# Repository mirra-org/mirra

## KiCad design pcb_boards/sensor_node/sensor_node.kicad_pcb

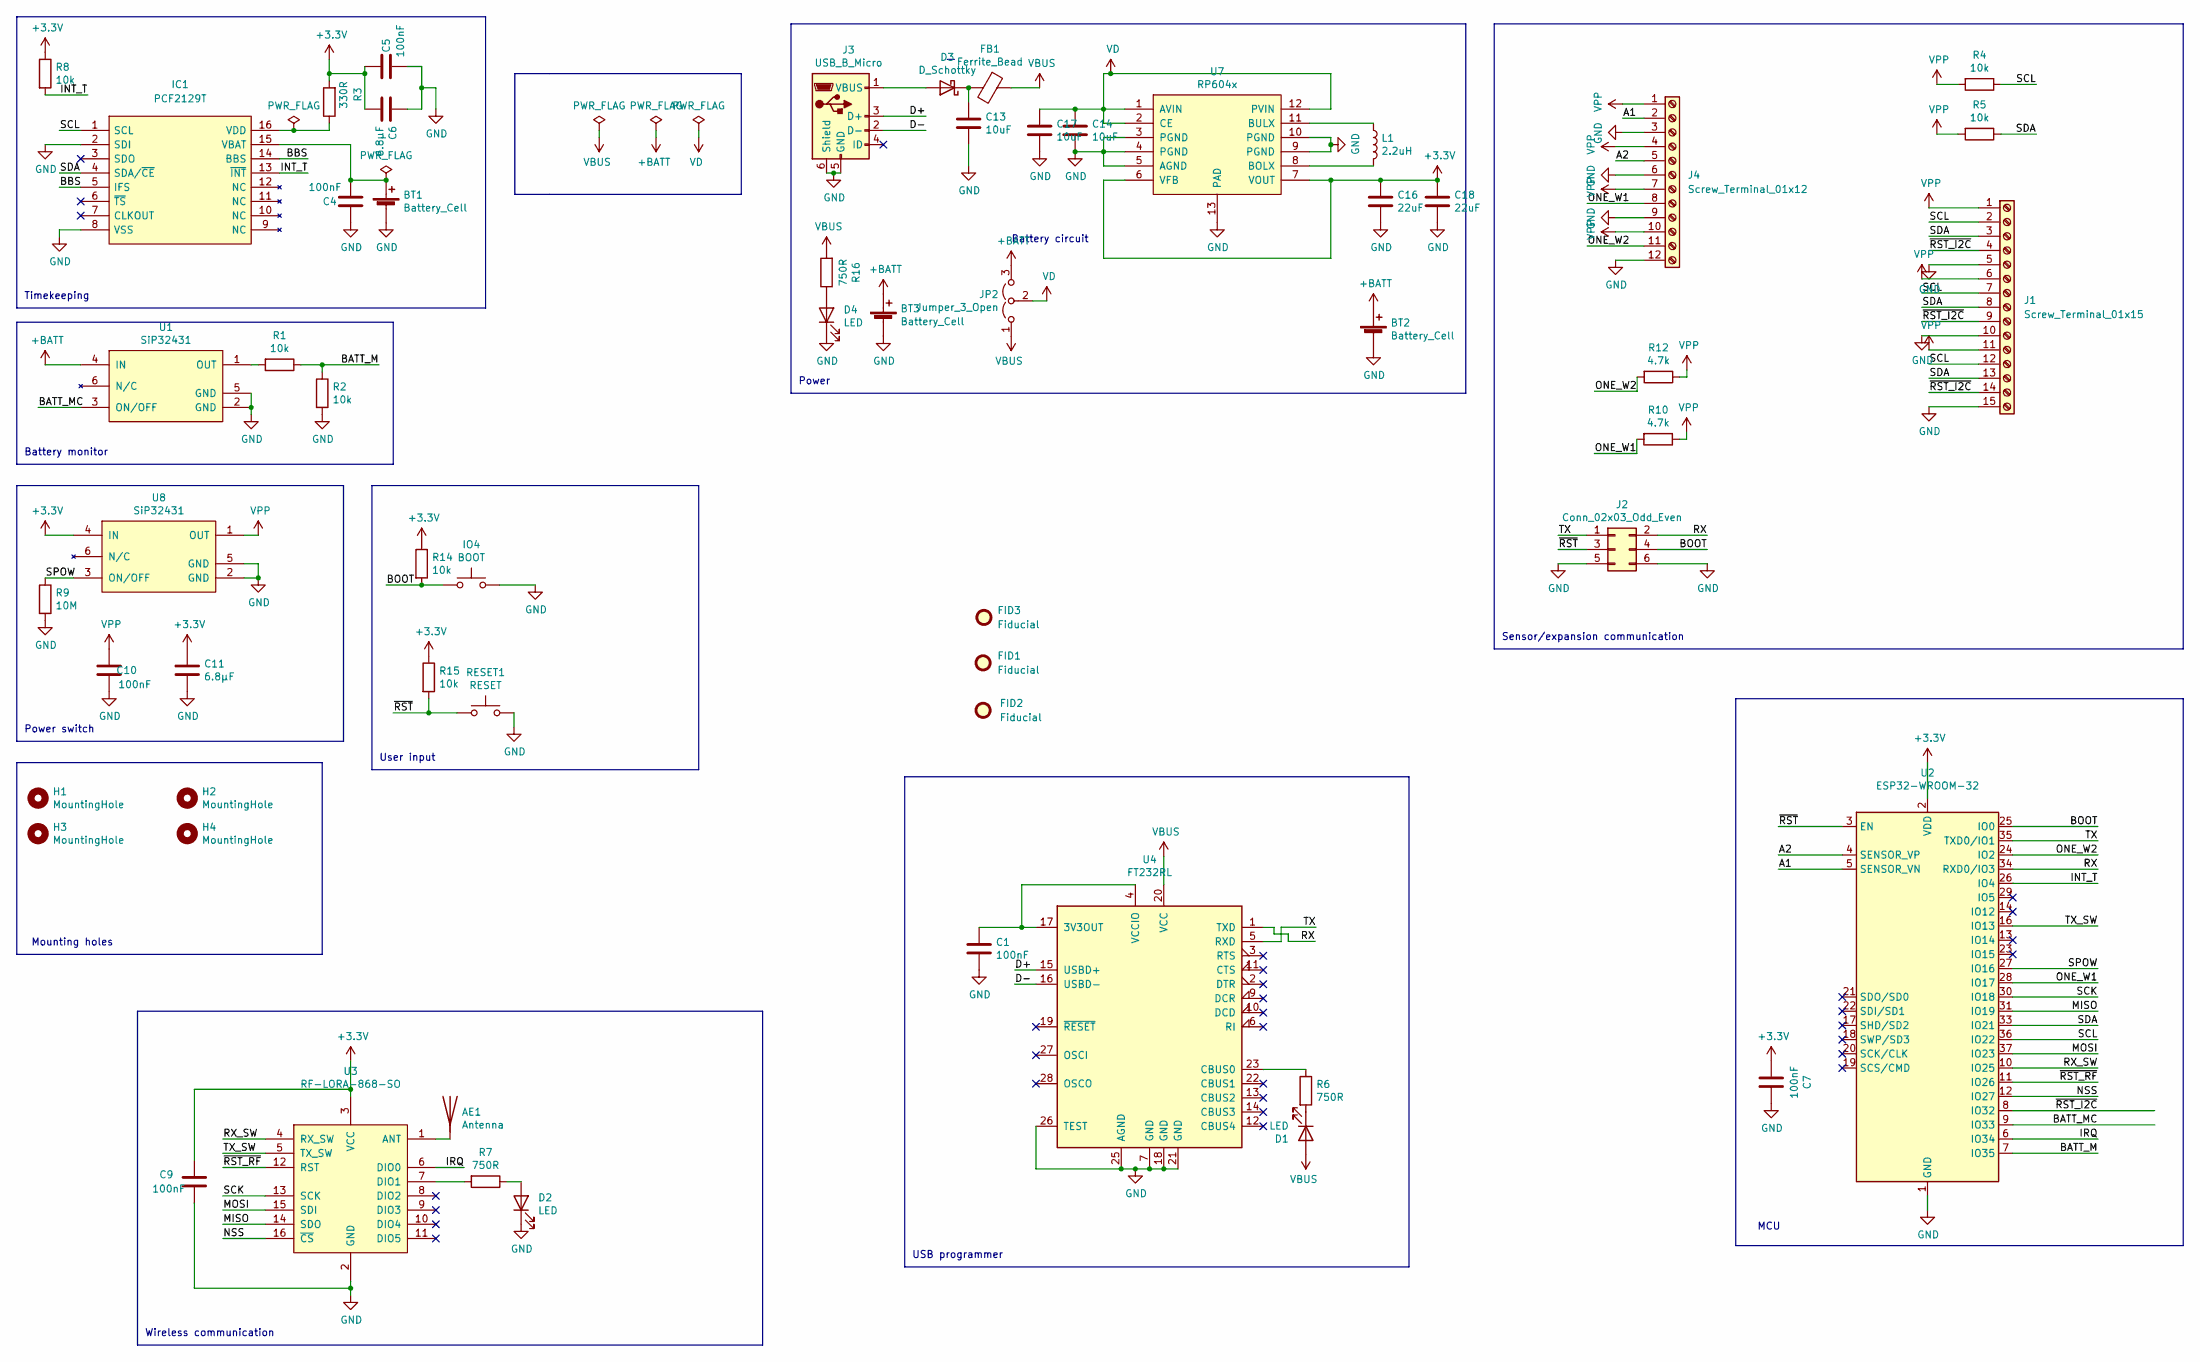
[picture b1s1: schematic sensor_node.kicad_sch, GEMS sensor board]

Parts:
AE1: Antenna; PinHeader_1x01_P2.54mm_Vertical
BT1: Battery_Cell; Renata_Battery_Holder_SMTM1125; Manufacturer_Part_Number SMTM1225; Mouser 614-SMTM1225
BT2: Battery_Cell; JST_EH_B02B-EH-A_1x02_P2.50mm_Vertical; Manufacturer_Part_Number B2B-EH-A(LF)(SN); Mouser 2399159
BT3: Battery_Cell; Eagle_Battery_Holder_A_12BH311P-GR; Manufacturer_Part_Number 12BH311P-GR; Farnell battery AA 1365937
C1: 100nF; C_0603_1608Metric; Mouser 810-CGA3E2X8R1E104K
C4, C5, C7, C9, C10: 100nF; C_0603_1608Metric; Manufacturer_Part_Number CGA3E2X8R1E104K; Mouser 810-CGA3E2X8R1E104K
C6, C11: 6.8µF; C_1206_3216Metric; Manufacturer_Part_Number CGA5L1X7R1C685MC; Mouser 810-CGA5L1X7R1C685MC
C13, C14, C17: 10uF; C_1206_3216Metric; Manufacturer_Part_Number TMK325BJ106KM-P; Mouser 963-TMK325BJ106KM-P
C16, C18: 22uF; C_1206_3216Metric; Manufacturer_Part_Number TMK316BBJ226ML-T; Mouser 963-TMK316BBJ226ML-T
D1: LED; LED_0603_1608Metric; Mouser TLMG1100-GS08
D2, D4: LED; LED_0603_1608Metric; Manufacturer_Part_Number TLMY1000; Mouser 78-TLMY1000
D3: D_Schottky; D_SMB; Manufacturer_Part_Number TLMY1000; Mouser 78-TLMY1000
FB1: Ferrite_Bead; L_0805_2012Metric_Pad1.15x1.40mm_HandSolder; Manufacturer_Part_Number MI0805K400R-10; Mouser 875-MI0805K400R-10
FID1, FID2, FID3: Fiducial; Fiducial_1mm_Mask2mm
H1, H2, H3, H4: MountingHole; MountingHole_3.2mm_M3
IC1: PCF2129T; SO16; Manufacturer_Part_Number PCF2129AT/2,518; Mouser Part Number 771-PCF2129AT/2,518
IO4: BOOT; SW_SPST_KMR2; Manufacturer_Part_Number KMR621NGLFS; Mouser 611-KMR621NGLFS
J1: Screw_Terminal_01x15; TerminalBlock_Phoenix_PTSA-1,2-2-3,5-F-THR-1x15-P3.50mm_45D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; Manufacturer_Part_Number 1985098; Mouser 651-1985098
J2: Conn_02x03_Odd_Even; PinHeader_2x03_P2.54mm_Vertical; Manufacturer_Part_Number 944-10-080-00
J3: USB_B_Micro; USB_Micro-B_Molex-105133-0001; Manufacturer_Part_Number 105017-0001; Mouser 538-105017-0001
J4: Screw_Terminal_01x12; TerminalBlock_Phoenix_PTSA-1,2-2-3,5-F-THR-1x12-P3.50mm_45D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; Manufacturer_Part_Number 1985069; Mouser 651-1985069
JP2: Jumper_3_Open; PinHeader_1x03_P2.54mm_Vertical; Manufacturer_Part_Number 4-103321-5; Mouser 571-4-103321-5
L1: 2.2uH; L_L4mm_D4mm_H1.8mm; Manufacturer_Part_Number TYS40182R2M-10; Mouser TYS40182R2M-10
R1, R2, R4, R5, R8, R14, R15: 10k; R_0603_1608Metric; Manufacturer_Part_Number APC0603B10K0N; Mouser 284-APC0603B10K0N
R3: 330R; R_0603_1608Metric; Manufacturer_Part_Number RC0603JR-07330RL; Mouser 603-RC0603JR-07330RL
R6, R7, R16: 750R; R_0603_1608Metric; Manufacturer_Part_Number RC0603FR-07750RL; Mouser 603-RC0603FR-07750RL
R9: 10M; R_0603_1608Metric; Manufacturer_Part_Number CRCW060310M0FKEAC; Mouser 71-CRCW060310M0FKEAC
R10, R12: 4.7k; R_0603_1608Metric; Manufacturer_Part_Number CRCW06034K70JNEAC; Mouser 71-CRCW06034K70JNEAC
RESET1: RESET; SW_SPST_KMR2; Manufacturer_Part_Number KMR621NGLFS; Mouser 611-KMR621NGLFS
U1, U8: SiP32431; SOT-363_SC-70-6; Manufacturer_Part_Number SIP32431DR3-T1GE3; Mouser 781-SIP32431DR3-GE3
U2: ESP32-WROOM-32; Manufacturer_Part_Number ESP32-WROOM-32D-N16; Mouser 356-ES32WROOM32D16MB
U3: RF-LORA-868-SO; RF-LORA-868-SMT; Manufacturer_Part_Number RF-LORA-868-SO; Mouser Farnell: 2500100
U4: FT232RL; SSOP-28_5.3x10.2mm_P0.65mm; Manufacturer_Part_Number FT232RL; Mouser 895-FT232RL
U7: RP604x; DFN_12_Pin_2.7x3mm_P0.5mm; Manufacturer_Part_Number RP604K331A-TR; Mouser 848-RP604K331A-TR

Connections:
+3.3V: C5.1, C6.2, C7.2, C9.1, C11.1, C16.1, C18.1, R3.2, R8.1, R14.1, R15.1, U2.2 (VDD), U3.3 (VCC), U7.6 (VFB), U7.7 (VOUT), U8.4 (IN)
+BATT: BT2.1 (+), BT3.1 (+), JP2.3 (B), U1.4 (IN)
/A1: J4.2, U2.5 (SENSOR_VN)
/A2: J4.5, U2.4 (SENSOR_VP)
/BATT_M: R1.1, R2.1, U2.7 (IO35)
/BATT_MC: U1.3 (ON/OFF), U2.9 (IO33)
/BBS: IC1.5 (IFS), IC1.14 (BBS)
/BOOT: IO4.1, J2.4, R14.2, U2.25 (IO0)
/D+: J3.3 (D+), U4.15 (USBD+)
/D-: J3.2 (D-), U4.16 (USBD-)
/INT_T: IC1.13 (~INT), R8.2, U2.26 (IO4)
/IRQ: U2.6 (IO34), U3.6 (DIO0)
/MISO: U2.31 (IO19), U3.14 (SDO)
/MOSI: U2.37 (IO23), U3.15 (SDI)
/NSS: U2.12 (IO27), U3.16 (~CS)
/ONE_W1: J4.8, R10.2, U2.28 (IO17)
/ONE_W2: J4.11, R12.2, U2.24 (IO2)
/RX: J2.2, U2.34 (RXD0/IO3), U4.1 (TXD)
/RX_SW: U2.10 (IO25), U3.4 (RX_SW)
/SCK: U2.30 (IO18), U3.13 (SCK)
/SCL: IC1.1 (SCL), J1.2, J1.7, J1.12, R4.1, U2.36 (IO22)
/SDA: IC1.4 (SDA/~CE), J1.3, J1.8, J1.13, R5.1, U2.33 (IO21)
/SPOW: R9.1, U2.27 (IO16), U8.3 (ON/OFF)
/TX: J2.1, U2.35 (TXD0/IO1), U4.5 (RXD)
/TX_SW: U2.16 (IO13), U3.5 (TX_SW)
/~RST_I2C: J1.4, J1.9, J1.14, U2.8 (IO32)
/~RST_RF: U2.11 (IO26), U3.12 (RST)
/~RST: J2.3, R15.2, RESET1.1, U2.3 (EN)
GND: BT1.2 (-), BT2.2 (-), BT3.2 (-), C1.2, C4.1, C5.2, C6.1, C7.1, C9.2, C10.2, C11.2, C13.1, C14.1, C16.2, C17.1, C18.2, D2.1 (K), D4.1 (K), IC1.2 (SDI), IC1.8 (VSS), IO4.2, J1.5, J1.10, J1.15, J2.5, J2.6, J3.5 (GND), J3.6 (Shield), J4.3, J4.6, J4.9, J4.12, R2.2, R9.2, RESET1.2, U1.2 (GND), U1.5 (GND), U2.1 (GND), U2.15 (GND), U2.38 (GND), U2.39 (GND), U3.2 (GND), U4.7 (GND), U4.18 (GND), U4.21 (GND), U4.25 (AGND), U4.26 (TEST), U7.3 (PGND), U7.4 (PGND), U7.5 (AGND), U7.9 (PGND), U7.10 (PGND), U7.13 (PAD), U8.2 (GND), U8.5 (GND)
unnamed: AE1.1 (A), U3.1 (ANT)
unnamed: BT1.1 (+), C4.2, IC1.15 (VBAT)
unnamed: D1.1 (K), R6.2
unnamed: D2.2 (A), R7.1
unnamed: D3.2 (A), J3.1 (VBUS)
unnamed: C13.2, D3.1 (K), FB1.2
unnamed: D4.2 (A), R16.1
unnamed: IC1.16 (VDD), R3.1
unnamed: R1.2, U1.1 (OUT)
unnamed: R7.2, U3.7 (DIO1)
unnamed: C1.1, U4.4 (VCCIO), U4.17 (3V3OUT)
unnamed: R6.1, U4.23 (CBUS0)
unnamed: L1.2, U7.8 (BOLX)
unnamed: L1.1, U7.11 (BULX)
VBUS: D1.2 (A), FB1.1, JP2.1 (A), R16.2, U4.20 (VCC)
VD: C14.2, C17.2, JP2.2 (C), U7.1 (AVIN), U7.2 (CE), U7.12 (PVIN)
VPP: C10.1, J1.1, J1.6, J1.11, J4.1, J4.4, J4.7, J4.10, R4.2, R5.2, R10.1, R12.1, U8.1 (OUT)

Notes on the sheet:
Power switch
USB programmer
Wireless communication
Timekeeping
User input
MCU
Battery circuit
Sensor/expansion communication
Battery monitor
Mounting holes
Power

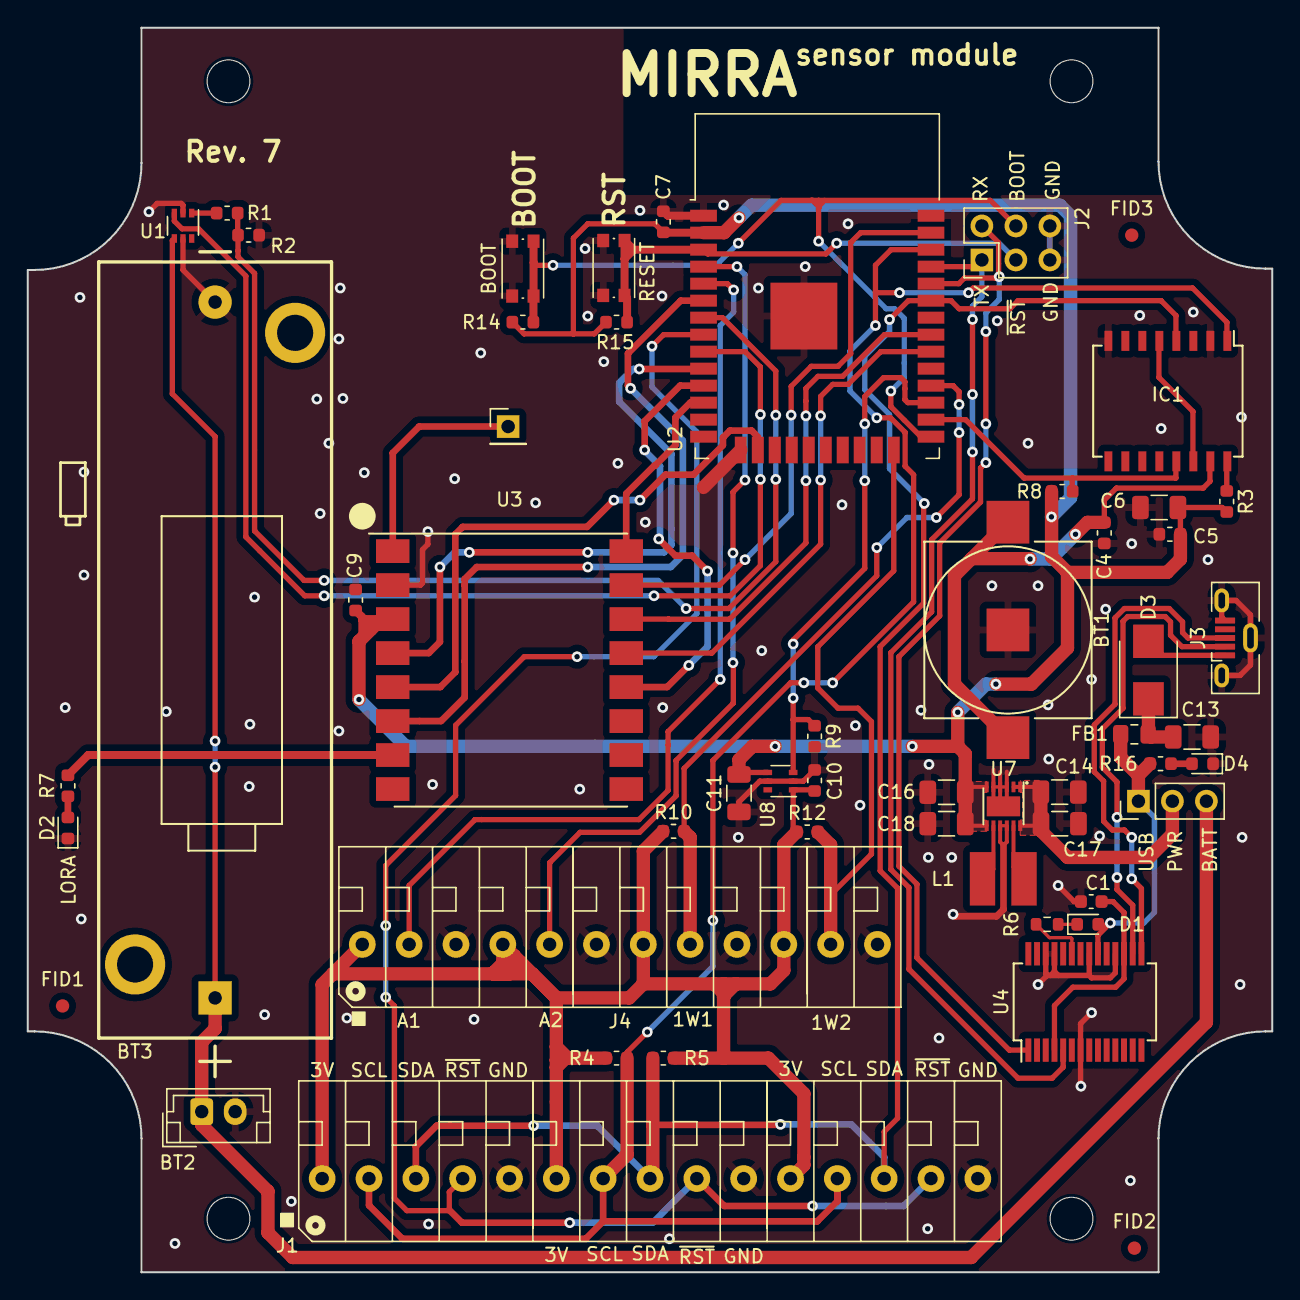
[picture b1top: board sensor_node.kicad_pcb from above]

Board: 2 copper layers, 93.0 x 93.0 mm, 58 parts (0 on the bottom side), 46 nets.

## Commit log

2024-01-26 Implement proper backspacing in command line
2024-01-28 Slightly optimise MACAddress::fromString
2024-02-01 Initial steps of comm redux Drastically alter messages, reducing header size and different message types. Introduce MIRRAAddress in place of MACAddress. Idea is to implement a variant on Selective AR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
2024-02-01 Invert discovery conversation; sensor node takes initiative
2024-02-12 Log prints to serial prints in rtcUpdateTime
2024-02-12 Fix SoilTemperatureSensor address resolution
2024-02-12 Rework config header files
2024-02-13 Reset timeout timer on every character entered
2024-02-13 Implement PSK support for MQTT upload
2024-03-11 Improve DallasTemperature usage
2024-03-25 Fix narrowing warnings
2024-03-25 Remove logfiles according to maxSize This removes the old daysTokeep method.
2024-03-25 Finalise changeServer(), implement setup()
2024-03-25 Change MQTT_SERVER
2024-03-25 Correct listenMessage
2024-03-29 Add MIRRA logo
2024-04-08 Only reduce logfileSizeSum when file removed
2024-04-08 Add rtcreset command Make SNTP more robust Start work on changeIntervals
2024-04-08 Fix maxSize in KiB in pruneLogfiles
2024-04-08 Remove ESPCam sensor
2024-04-08 Commands system improvements Implement implicit parsing of arithmetic args Add various helper methods Add echoNum command
2024-04-08 Fix bug in editValue
2024-04-08 Formatting
2024-04-08 Remove StreamDebugger
2024-04-08 Add getName to Sensor interface
2024-04-08 Add clangtidy
2024-04-08 Add rtcReset command
2024-04-08 Add common commands to MIRRAModule
2024-04-08 Inherit from MIRRAModule::Commands
2024-04-22 Header inclusion optimisations
2024-04-22 Improve MQTT upload on error Also use new editValue functions for changeServer and changeWifi
2024-04-22 Adjust MAX_SENSORDATA_FILESIZE
2024-04-22 Finalise changeIntervals
2024-05-12 Initialise mkdocs documentation
2024-05-12 Upsize data partition
2024-05-12 Remove grafana; further Docker clean-up
2024-05-12 Alter MQTT broker config path
2024-05-12 Add Caddy HTTPS port forwarding
2024-05-12 Switch USB programmer UART lines; fix LED
2024-05-13 Slightly downsize data partition
2024-05-13 Log reset reason on boot
2024-05-28 Make USB connector vertical; fix tiny errors
2024-07-02 Add various GCC args for warnings
2024-07-02 Alter namespace indentation rule
2024-07-02 Additional progress on comm redux
2024-07-03 Add support for Shared sensor types
2024-07-03 Move NTP fetch log into conditional
2024-07-03 Define nvs, logs and sensor data partitions
2024-07-03 Add first NVS/File abstractions
2024-07-04 Finalise NVS
2024-07-04 Fix SharedSensor not using proper CRTP
2024-07-04 Wait 10ms after peripheral power-up
2024-07-04 Slightly alter partitions with consistent sizing
2024-07-04 Add File class/interface
2024-07-04 Implement File::read/write, add NVS::exists
2024-07-05 Rename sensor -> data partition
2024-07-05 Fix various issues in FS, NVS
2024-07-05 Add first FIFOFile
2024-07-07 Finale first FS version
2024-07-07 Remove reduntant FIFOFile files
2024-07-07 Alter formatting rules
2024-07-07 Update logging to work with new FS
2024-07-09 Remove src folder in logging lib
2024-07-17 FS integration with MIRRAModule/Logging
2024-07-17 Remove filepaths from config
2024-07-17 Integrate FS with gateway
2024-07-19 Integrate FS with sensor node
2024-07-19 Fix lingering use of message vs entry
2024-07-19 Import mirra namespace
2024-07-20 Remove Flags from Message<SENSOR_DATA>
2024-07-20 Alter ordering of time/nValues in sensor entry/message
2024-07-20 Apply formatting
2024-07-20 Add clang-tidy config
2024-07-20 Fix too early address advancement
2024-07-20 Add SensorFile iteration + data readout commands
2024-07-20 Make timeLength static constexpr
2024-07-20 Break braces before else/after control
2024-07-20 Show space on printData; intialise SensorFile properly
2024-07-20 Do not sort using declarations
2024-07-20 Add format command
2024-07-20 Add NVS error logging, deinit function
2024-07-20 Fix no return warning
2024-07-20 Make Log() explicit constructor
2024-07-20 Further modify partitions
2024-07-20 Fix buffer overflow in Partition::name, ::part null pointer
2024-07-20 Use Log::getInstance for init of static log singleton
2024-07-21 Fix buffer overflow in Log::print
2024-07-21 Add Log::close method
2024-07-21 Update partitions to avoid boot loop
2024-07-21 FIx various FS bugs Fix sectorbuffer dereferencing in write/read Remove exists method Make NVS::get return optional Add proper error messaging
2024-07-25 Fix bug in Partition::read reading stale flash
2024-07-25 Fix flagsPosition in SensorFile Fix hex dump formatting issue
2024-07-25 Move printLogs Command to MIRRAModule
2024-07-26 Add spam command Fix lingering flagsPosition in setUplaoded
2024-07-26 Add esp32 exception decoder filter
2024-07-26 Fix NVS::Value constructor without defaultValue
2024-08-13 Minor work on Protocol Rename depush -> pop Further develop Protocol::receive Rename prepush -> push with single arg
2024-08-13 Minor fixes to CommCommon Remove maxWindowSize
2024-08-13 Make Protocol friend class of LoRaModule
2024-08-14 Improve Window interface
2024-08-26 Add NVS erase key/value function
2024-08-26 Rename loadNodes/storeNodes, remove removeNode
2024-09-10 Light Sensor returns lux values instead of raw
2024-09-10 Alter MessageHeader constructor
2024-09-10 Add sendAcks, fix ms
2024-09-10 Type of typeTag uint32_t -> uint8_t
2024-09-10 Add automatic PSK sharing
2024-09-10 Add COMMAND_TIMEOUT CommandCode
2024-09-10 Fix minor typo in uploadPeriod
2024-09-11 Add testmqtt command
2024-09-12 Adjust PSK retrieval logic: use header for MAC
2024-09-13 Slightly increase program partition
2024-09-13 Correct generation of node keys for storeNodes
2024-09-13 Add error messaging to NVS::set_blob
2024-09-13 Correct exit command not exiting
2024-09-13 Add const-qualified getAddress
2024-09-13 Flush on FIFOFile destructor
2024-09-13 Add server, interval commands
2024-09-13 Revert flush on FIFOFile destructor
2024-09-14 Add psk/client identity to MQTTClient
2024-09-14 Slightly increase NVS partition size
2024-09-14 Remove redundant gpio_hold_dis
2024-09-14 Refactor to fs::NVS, fixes inconsistent saving of values
2024-09-14 Add FS test (NVS only for now)
2024-09-15 Rename MIRRACommunicationCommon
2024-09-23 Finalise bulk of protocol core Fix LoRaModule not going into standby after rx/tx
2024-09-24 Begin integration of Protocol core with main code
2024-10-01 Fix SensorFile::push for Message<SENSOR_DATA> Change partition sizes yet a-gain
2024-10-15 Huge webserver overhaul Merge mqtt broker, parser and webapp into one container Add Vite/Typescript-powered frontend built around HTMX, pnpm as package manager Add FastAPI python backend with SQLite 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
2024-10-15 Add logo Illustrator file
2024-10-15 Remove kicad lock
2024-10-15 Add node_modules, deploy_db to .gitignore
2024-10-15 Add empty mirra_backend.env
2024-10-15 Add mqtt_enabled config variable, db_prefill variable
2024-10-17 Add .env to .gitignore
2024-10-17 Upgrade to Python 3.12
2024-10-17 Reorder startup code into app's lifespan function Add empty mock classes for MQTT broker & parser, these will be used in the event that MQTT is disabled Fix global_init in tests
2024-10-17 Add default and test prefills
2024-10-17 Update prepopulation Configure tests to use new prepopulation method Move DBPrefill outside Config class
2024-10-17 Minor syntax improvements
2024-10-17 Move aio.run outside of except block
2024-10-17 Check DB and prepopulate in configure_db
2024-10-17 Add Vite HMR client, fix bug in attrs for script tags
2024-10-21 Add htpy; migrate all templates to htpy expressions
2024-10-29 Move max nodes check to after node recognition
2024-10-29 Remove lit
2024-10-29 Reorder global_init in configure_db
2024-10-29 Improve logging - no more `print`s
2024-11-05 Alter partition tables to avoid NVS erasure
2024-11-05 Add logs to .gitignore
2024-11-05 Update decode_uart script
2024-11-08 Add more client-side validation for adding gateway
2024-11-08 Register exception handler early
2024-11-08 Add node removal function and command
2024-11-08 Increase MAX_SENSOR_NODES hardcode to 35
2024-11-08 Remove UPLOAD_EVERY functionality Upload after every comm period instead
2024-11-08 Remove MAX_SENSORDATA_FILESIZE, adjust MQTT_PORT
2024-11-11 Add insertion_timestamp column in measurement table
2024-11-11 Bump mirra-web base containter to Python 3.12
2024-11-12 Fix insertion timestamp type mismatch
2024-11-12 Add addNode command
2024-11-12 Finalise decode_uart script
2024-11-12 Remove auto_capitalize attribute; causes forms to GET (?)
2024-11-24 Move remaining RTC attributes to NVS
2024-11-24 Update README with new/updated commands
2024-11-24 Remove redundant `.vscode` and `.idea` directories
2024-11-28 Properly destruct Gateway::Parameters before sleep
2024-11-28 Clear Control_2 flags on PCF2129 init
2024-11-29 Remove async tag from vite assets Causes race condition for script loading e.g. HTMX
2024-12-05 Add insertion_timestamp to prepopulation
2024-12-05 Remove prepopulation_sync
2024-12-05 Slightly optimise CSV export with inner joins
2024-12-07 Drastically improve db performance for timestamp queries
2025-02-12 Remove misleading manual PSK entry prompt
2025-02-14 Correct some command descriptions
2025-02-14 Remove internal pullup resistor on RTC interrupt pin The PCB already contains one.
2025-05-20 Remove "ArduinoHttpClient" dependency Redudant; we already use ESP32's HTTP libs
2025-06-02 Add restart unless-stopped option to mirra_web container
